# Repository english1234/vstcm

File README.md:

# VSTCM - the v.st Colour Mod - a colour vector graphics generator
The vstcm is a vector signal transceiver PCB which generates colour vector graphics to be displayed on an oscilloscope or vector monitor such as Amplifone, Wells Gardner WG6100, Hantarex MTRV and Electrohome G05, as used in Star Wars, Tempest, Gravitar, etc. 

When used with a computer (Raspberry Pi, PC, ...) running AdvanceMAME, it can be used to play classic colour (and monochrome) vector arcade games, but it can also play certain games all by itself using various emulators. If you search for vstcm on a well-known video sharing site you can see the board in action.

(Haven't got a vector monitor or an oscilloscope? Make your own, it's not that hard! - see below).

For those who built a V2 of this board, a document is provided to convert the wiring to run with V3 software.

The original v.st was designed by Trammell Hudson for black & white games. Documentation for that version can be found here https://github.com/osresearch/vst and here https://trmm.net/V.st/

Compared to the original version, the new vstcm adds:
- RGB colour with different intensity levels
- 6502, Z80 and 6809 emulators which allows it to play games on its own without a Raspberry Pi or MAME
- A mini version of MAME for playing vector games on the Teensy without a Raspberry Pi
- An upgrade to the Teensy 4.1 for more power (eg >800Mhz as opposed to 120Mhz for the Teensy 3.2)
- Asteroids style test patterns in Red, Green & Blue to aid CRT convergence
- A configuration menu with settings stored on the built in SD card
- Programmable onboard control buttons
- Programmable IR remote control buttons
- Extra pots to control X & Y position (to complement the existing X & Y size pots)
- Several power supply options: either USB, or external 5V/9V/12V

The board was built with simplicity in mind using components that are easy to find, and easy to solder so that anyone can build one.

## Programme code

Currently, the board can work in either of two ways:
- connected to a Raspberry Pi running MAME. The programme code for this option is a development of that which was provided with the original version of the v.st, with modifications made by "Swapfile" (Github user) to interface with AdvanceMAME, and then further modifications made by myself in order to add the new functionality specific to the vstcm, followed by extensive optimisation by fcawth (cf his fork of this project). There is scope for further improvement (see the wiki for this project in the link above), and it is hoped that the publication on github will encourage contributions to develop this as a relatively cheap and easy solution for the vector arcade / vector graphics community.
- on its own, running a 6502, Z80 or 6809 emulator, and with the original game ROM files stored on the SD card of the Teensy. So far, Battlezone, Asteroids and Donkey Kong work with this, but it shouldn't be too much trouble to get others working. Sound and external controls have not been properly implemented as yet (please feel free to contribute the necessary mods to the code...). See instructions below for how to get this to work.

## History of development

For those interested in seeing how things got to this point, the inital development of the PCB was documented with plenty of pictures (in French, but use Google Translate if required) here : https://www.gamoover.net/Forums/index.php?topic=43469.0 (from page 5) and also shows previous work on building vector arcade HV boards, an Amplifone deflection reproduction, an Asteroids game PCB reproduction, a bit of yoke rewinding, etc.

If you want to get in touch to ask questions, or contribute, I can be contacted at: robin@robinchampion.com or on Github (user english1234), Gamoover (english2), UKVAC (english2), KLOV (english2), as well as via the various vector graphics/Vectrex forums on Facebook.

A dedicated vstcm web page can be found here: https://robinchampion.com/vst_colour_mod.htm

Thread on KLOV: https://forums.arcade-museum.com/threads/announcing-the-vstcm-colour-vector-generator.505940/

Thread on UKVAC: http://www.ukvac.com/forum/announcing-the-vstcm-colour-vector-generator_topic388998_page1.html

## Getting the PCB built

A ZIP file is in the Gerbers directory. This can be uploaded to your PCB manufacturer of choice. It's a 2 sided 10cm x 10cm board so should be extremely cheap (JLPCB charged less than 5€ / $5 + shipping for 10 pieces in May 2022).

## Components

The BOM is in a dedicated folder and has Mouser references for many parts at the right hand side. 

- IC2: You need to choose if you are going to use an external supply or not and if so what voltage to use (5V, 9V or 12V). Recom makes these parts, but so do Traco and there may be other brands. Make sure there is a D (for double) at the end of the model number which generates +/- voltages, rather than the S (single) version. See power options below.
- The Molex parts are not strictly necessary, you may prefer something different or simply to solder wires directly to the holes in the PCB.
- U5: See power options below. I have also used a 7805 as a direct replacement with a small heatsink on it, which gets quite warm but hasn't burnt out as yet.
- optional IR remote: I really recommend this if you are putting the board inside a cabinet - see "IR remote programmable control buttons" below.
 
I would recommend socketing everything on the board (Teensy, DACs, Op Amps) so that they can be swapped out if better choices are found in the future.

Make sure you order short resistors, space for them on the board is tight.

## Power options for the PCB

The PCB can be powered in several ways (connect to J6):

|N° | Power supply option              | Supplies                                    | C3/C4    | IC2      | U5/C19/C20  | Split pad Teensy | Tested |
|---|----------------------------------|---------------------------------------------|----------|----------|-------------|------------------|--------|
| 1 | USB 5V                           | Complete circuit inc Teensy                 | Required | RB-0512D | Absent      | No               | No     |
| 2 | USB 5V + external 5V unregulated | USB supplies Teensy, external supplies rest | Required | RB-0512D | Absent      | No               | Yes    |
| 3 | External 9V unregulated          | Complete circuit inc Teensy                 | Required | RB-0912D | Present     | Yes              | No     |
| 4 | External 12V unregulated         | Complete circuit inc Teensy                 | Required | RB-1212D | Present     | Yes              | Yes    |
| 5 | USB 5V + external 12V regulated  | USB supplies Teensy, external supplies rest | Absent   | Absent   | Absent      | No               | Yes    |

1/ power the whole thing via USB from a Raspberry Pi: This requires a short good quality USB cable to work reliably. Make sure the Pi has at least a 3A supply. Since U5 is absent, bridge the two outer pins with a jumper wire.

2/ power the Teensy via USB from a Raspberry Pi, and use a separate external supply (such as a wall wart) for the DACs and Op Amps. 

3 & 4/ power the whole thing via an external supply which can be 9V or 12V (not 5V): this requires adding a LM2940T-5.0 regulator at U5 along with it's associated caps at C19 & C20, as well as cutting a link on the Teensy to ensure that it doesn't receive conflicting power from both the USB and the external supply. The RB-xx12D needs to be either a 9V or 12V model depending on the voltage of the external supply. A 5V supply won't work as the LM2940 requires over 6V to function according to its datasheet. 

The choice is really just a matter of what you have on hand. It makes no difference what vector CRT you have, as the output voltages of the PCB are the same whatever you use to power it. If you're connecting to an existing arcade machine, then chances are you have a +/-12V supply coming out of the power brick. Otherwise, many people have a box of old "wall wart" 5V (or 9V or 12V) adapters which will work fine: either fit a barrel connector to the PCB input or chop the connector off the end of the power supply and solder the 2 wires directly to the board (check with a multimeter first which is positive and which is ground). 

The easiest option is to use a 5V (option 2) as the LM2940 is not required, and you don't need to cut the link on the Teensy to separate USB and external power.
Do not use J7 unless you have thoroughly understood how the schematic works for the power supply.

## Schematic

This may seem obvious, but it's worth downloading Kicad in order to view the schematic and the PCB as there are some build notes on the schematic, and it will help you to understand the main sections of the PCB and how it all connects together. For the lazier, a PDF is available.

## Programming the Teensy

Follow the instructions on this page to download and install the Arduino environment and Teensyduino extension: https://www.pjrc.com/teensy/td_download.html
Use the Arduino software to load the .ino file in the Teensy code directory.

Connect the Teensy via USB to your computer.

Choose the Teensy 4.1 in the Teensyduino options, and overclock to 816Mhz, as well as the "Fastest" option. Make sure you have the latest version of Teensyduino.

Press the compile button. You may need to add the Bounce2 library if you don't already have it.

Press the upload button (or the button on the Teensy if it doesn't upload automatically).

(You can also use PlatformIO if you prefer).

There is a more detailed guide "How to programme the Teensy with the code for the VSTCM PCB.pdf" in the root directory.

## Testing the vstcm

Once the board is built and the Teensy programmed and fitted, it can be connected to your deflection board of choice (it has been tested on Amplifone, Wells Gardner WG6100, Electrohome G05 and Hantarex MTRV so far) and when powered on should show a test screen. It may be necessary to change the size and positions pots on the PCB as well as other controls on the deflection board (such as Z or colour gain).

Before connecting to the deflection board, it would probably be a good idea to make sure the vstcm is generating appropriate voltages at its outputs (preferably with an oscilloscope, or failing that with a decent multimeter). 

If you want to save changes to settings shown on the onscreen menu, then put a SD card in the Teensy (formatted with FAT32). After changing the settings to your requirements and pressing the middle button on the PCB, the vstcm.ini file will be created at the root of the SD card so that they can be reloaded at each boot. 

## Testing Battlezone with the 6502 emulator

Put the following ROM files on a SD card in a directory called roms/Battlezone: 036414a.01, 036413.01, 036412.01, 036411.01, 036410.01, 036409.01, 036422.01, 036421.01 (it's up to you to find them from somewhere...).

Put the SD card in the slot on the Teensy.

Upload the bzone.ino to the vstcm using the Arduino software.

Plug it in.

Switch on! 

If you have a IR remote then you can control the game in a rather basic manner for the moment... (press OK to start)

## Testing games with AdvanceMAME

A Raspberry Pi 4 or 400 is recommended (I have also tested with a Pi 3 Model B+ 2017 and an Orange Pi 3 LTS which seem to work ok too). If you are running the vstcm from the Raspberry/Orange Pi then a 3A supply would be preferable.
Other options are Windows, a Linux VM under Windows, native Linux or Mac (the latter of which I have not yet tested). 
I followed the instructions here to download and compile AdvanceMAME: https://www.arcade-projects.com/threads/almost-pixel-perfect-arcade-emulation-on-raspberry-pi-with-advancemame.7777/

Basically, there are just 7 commands on the Pi which are as follows:

```sudo apt-get install git autoconf automake libsdl2-dev libasound2-dev libfreetype6-dev zlib1g-dev libexpat1-dev libslang2-dev libncurses5-dev

git clone https://github.com/amadvance/advancemame.git

cd advancemame

sh autogen.sh

./configure

make -j3

sudo make install
```

You need to find some ROMs from somewhere and copy them into the ROM folder. I'm sure you'll manage to find them... The easiest way to get them on to the Pi is to set up a Samba share and copy them over from a PC.

Then to launch, type advmame followed by the name of the game.

If you're not getting output over the USB cable to the vstcm, then check the advmame.rc file and at the bottom make sure you have vector_aux_renderer set to dvg (instead of none) and vector_aux_renderer_port set to /dev/ttyACM0

The AdvanceMAME protocol for the USB DVG is here: https://github.com/amadvance/advancemame/blob/master/advance/osd/dvg.c 

You can change the settings on the VSTCM during a game by pressing the left and right buttons on the PCB simultaneously to display the menu as an overlay.

## IR remote programmable control buttons

For £1 / $1 / 1€ you can get a HX1838 infra red adapter board with remote control, wiring, everything you need in fact. There are only 3 wires to connect: 5V, GND and signal. I soldered pin headers in the holes provided on either side of the Teensy, and put 5V on the bottom left hand hole of the Teensy (to left of USB socket), GND on the bottom right pin of the Teensy, and signal on pin 32 (top right hand pin of Teensy). 

This might seem like a bit of a gadget, but when you are spending your time going behind the arcade cab to press a button, coming back round the front to see the effect on the screen, and doing this over and over again, the advantages become obvious! 

The IR sensor is the size of an LED and so very easy to hide somewhere at the front of an arcade cab, and then you can just change the settings at will while you look at the screen.

## Haven't got a vector monitor or an oscilloscope?

Apart from this PCB, you need a CRT, a high voltage board, a deflection board and a power supply to make a complete vector monitor. There are solutions for all of these parts:

CRT - I'm using a 19"/48cm Philips TV bought for pennies through the small ads. You need to rewind the yoke using magnet wire. There is an excellent video by Jason Kopp here which explains all: https://youtu.be/Ci9qiGVMF7s I experimented on a 5" b&w security monitor first, then went for the big screen. Avoid Trinitrons and PC monitors, you need a basic no frills TV tube. It took me several attempts to get it more or less right, but I still have some wires which are not completely straight and the result seems to be the slightly bent vectors visible in the top right hand corner of my screen in the photo of the test screen above. The whole thing really wasn't hard, it just requires patience.

High voltage: Amplifone and Wells Gardner 6100 blank PCBs are available online, and there are also fully built solutions (see the various vector groups on Facebook) available new or second hand from the usual auction sites and specialist arcade sellers (mostly USA based).

Deflection board: I bought a second hand non working Amplifone and then fixed it (which wasn't hard, plenty of info online), but new PCBs are available online, and a Wells Gardner WG6100 should work too.

Power supply: the CRT and deflection board can be run either from an old Atari power brick, or else by wiring together two cheap 24V power supplies from Aliexpress in order to provide +/- 24V which satisfies the requirement for 50VAC on a Amplifone colour vector monitor. The CRT needs 6.3V for the heater filament, which I'm getting from an Atari power brick using the supply meant for the coin door, but there are other solutions if you look online (hint: 6.3V is frequently required for valve amp projects). If you find the right Atari power brick, it will power the whole thing: CRT, HV, deflection, Raspberry Pi and vstcm.

There's plenty of discussion of solutions to these problems on KLOV, UKVAC, and the FB vector forums with plenty of knowledgeable people able to answer questions. Also there are a fair few videos on Youtube going from theory to practice. Again, it's not that hard, so give it a go!

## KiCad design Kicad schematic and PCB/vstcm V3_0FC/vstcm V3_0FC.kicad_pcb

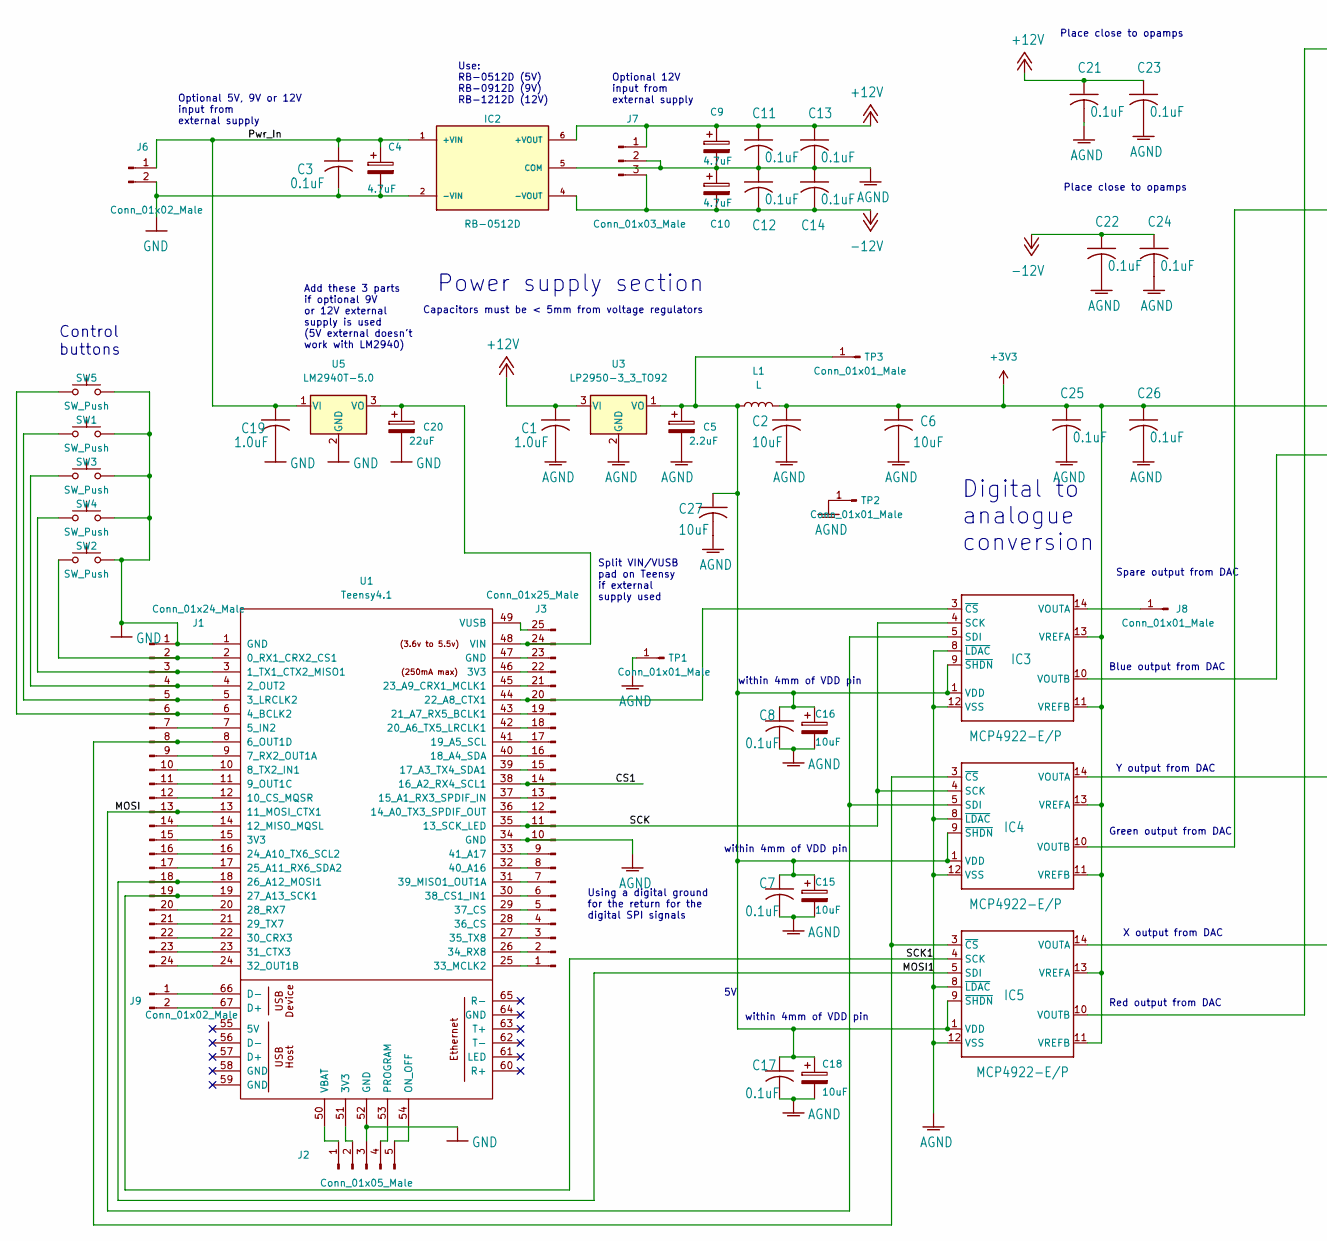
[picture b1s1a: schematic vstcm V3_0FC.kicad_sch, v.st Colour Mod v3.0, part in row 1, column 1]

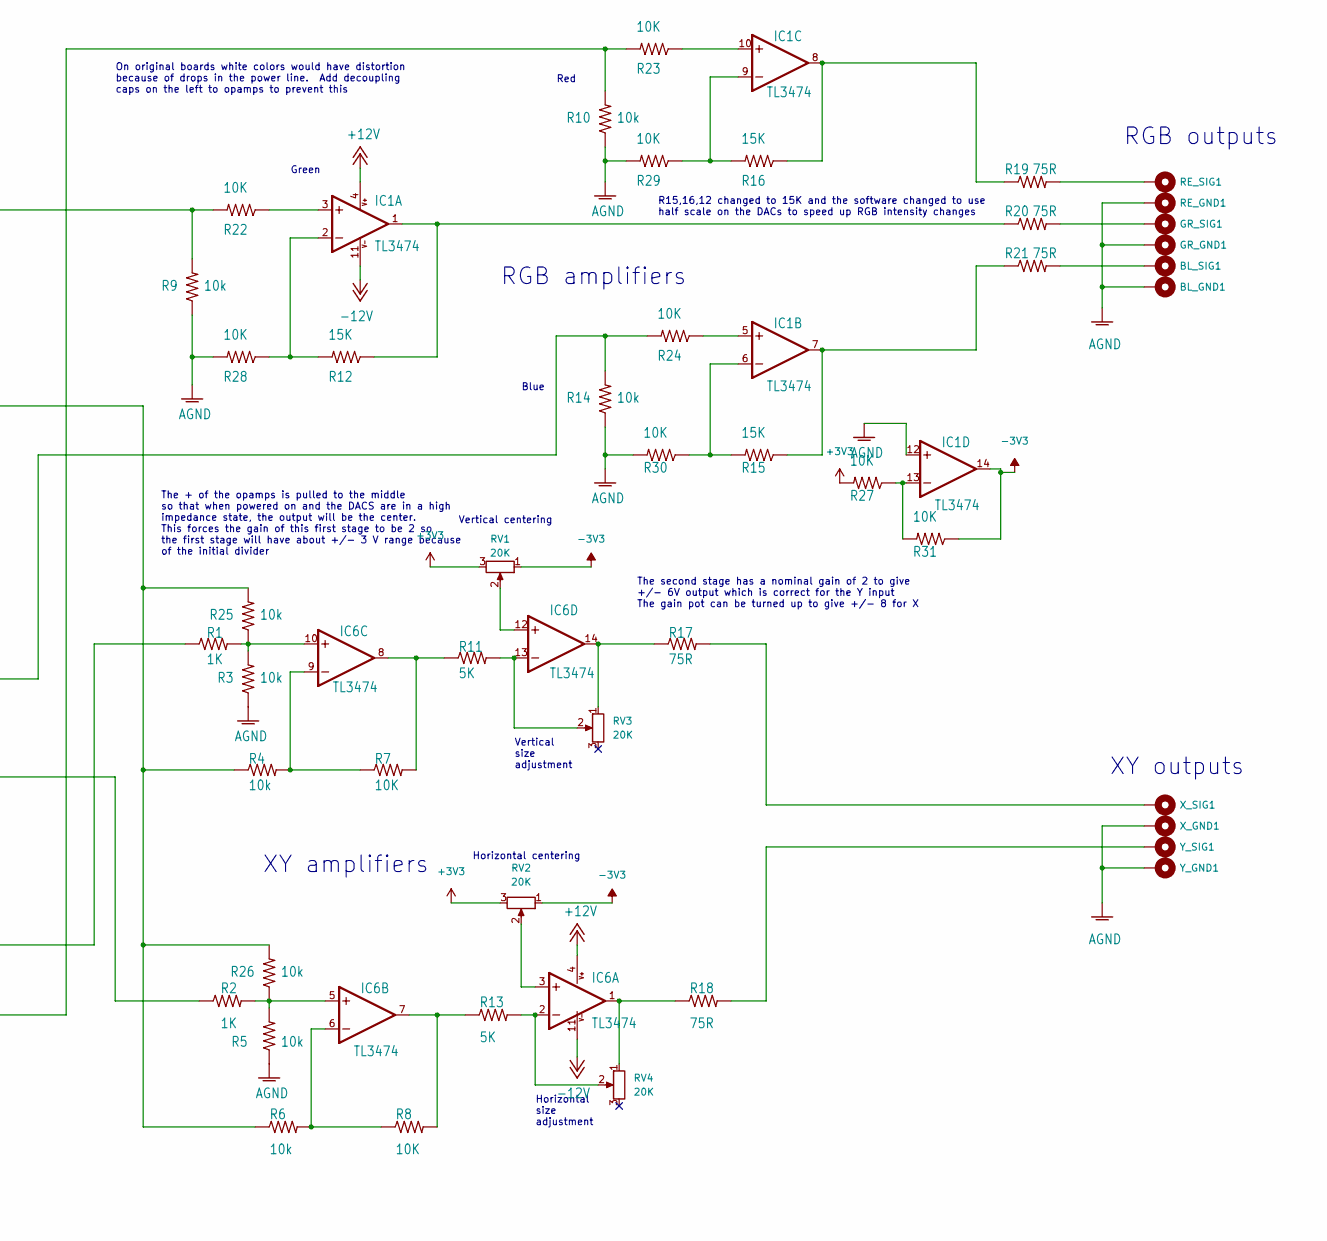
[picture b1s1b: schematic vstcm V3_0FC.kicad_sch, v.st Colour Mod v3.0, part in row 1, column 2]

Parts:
BL_GND1: MountingHole_Pad; MountingHole_2.2mm_M2_DIN965_Pad_TopBottom
BL_SIG1: MountingHole_Pad; MountingHole_2.2mm_M2_DIN965_Pad_TopBottom
C1, C19: 1.0uF; C_Disc_D5.0mm_W2.5mm_P2.50mm
C2, C6, C27: 10uF; C_Disc_D5.0mm_W2.5mm_P2.50mm
C3, C7, C8, C11, C12, C13, C14, C17, C21, C22, C23, C24, C25, C26: 0.1uF; C_Disc_D5.0mm_W2.5mm_P2.50mm
C4, C9, C10: 4.7uF; CP_Radial_D5.0mm_P2.00mm
C5: 2.2uF; CP_Radial_D5.0mm_P2.00mm
C15, C16, C18: 10uF; CP_Radial_D5.0mm_P2.00mm
C20: 22uF; CP_Radial_D5.0mm_P2.00mm
GR_GND1: MountingHole_Pad; MountingHole_2.2mm_M2_DIN965_Pad_TopBottom
GR_SIG1: MountingHole_Pad; MountingHole_2.2mm_M2_DIN965_Pad_TopBottom
IC1, IC6: TL3474; DIP-14_W7.62mm_Socket
IC2: RB-0512D; RECOM_0512D; PARTREV 0/2015
IC3, IC4, IC5: MCP4922-E/P; DIP-14_W7.62mm_Socket
J1: Conn_01x24_Male; PinHeader_1x24_P2.54mm_Vertical
J2: Conn_01x05_Male; PinHeader_1x05_P2.54mm_Vertical
J3: Conn_01x25_Male; PinHeader_1x25_P2.54mm_Vertical
J6: Conn_01x02_Male; Molex_KK-254_AE-6410-02A_1x02_P2.54mm_Vertical
J7: Conn_01x03_Male; Molex_KK-254_AE-6410-03A_1x03_P2.54mm_Vertical
J8: Conn_01x01_Male; PinHeader_1x01_P2.54mm_Vertical
J9: Conn_01x02_Male; PinHeader_1x02_P2.54mm_Vertical
L1: L; L_Axial_L12.0mm_D5.0mm_P15.24mm_Horizontal_Fastron_MISC
R1, R2: 1K; R_Axial_DIN0207_L6.3mm_D2.5mm_P7.62mm_Horizontal
R3, R4, R5, R6, R9, R10, R14, R25, R26: 10k; R_Axial_DIN0207_L6.3mm_D2.5mm_P7.62mm_Horizontal
R7, R8, R22, R23, R24, R27, R28, R29, R30, R31: 10K; R_Axial_DIN0207_L6.3mm_D2.5mm_P7.62mm_Horizontal
R11, R13: 5K; R_Axial_DIN0207_L6.3mm_D2.5mm_P7.62mm_Horizontal
R12, R15, R16: 15K; R_Axial_DIN0207_L6.3mm_D2.5mm_P7.62mm_Horizontal
R17, R18, R19, R20, R21: 75R; R_Axial_DIN0207_L6.3mm_D2.5mm_P7.62mm_Horizontal
RE_GND1: MountingHole_Pad; MountingHole_2.2mm_M2_DIN965_Pad_TopBottom
RE_SIG1: MountingHole_Pad; MountingHole_2.2mm_M2_DIN965_Pad_TopBottom
RV1, RV2, RV3, RV4: 20K; Potentiometer_Bourns_3386P_Vertical
SW1, SW2, SW3, SW4, SW5: SW_Push; SW_PUSH_6mm_H4.3mm
TP1, TP2, TP3: Conn_01x01_Male; PinHeader_1x01_P2.54mm_Vertical
U1: Teensy4.1; Teensy41
U3: LP2950-3_3_TO92; TO-92
U5: LM2940T-5.0; TO-220-3_Vertical
X_GND1: MountingHole_Pad; MountingHole_2.2mm_M2_DIN965_Pad_TopBottom
X_SIG1: MountingHole_Pad; MountingHole_2.2mm_M2_DIN965_Pad_TopBottom
Y_GND1: MountingHole_Pad; MountingHole_2.2mm_M2_DIN965_Pad_TopBottom
Y_SIG1: MountingHole_Pad; MountingHole_2.2mm_M2_DIN965_Pad_TopBottom

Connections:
+3V3: C2.1, C6.1, C25.1, C26.1, IC3.11 (VREFB), IC3.13 (VREFA), IC4.11 (VREFB), IC4.13 (VREFA), IC5.11 (VREFB), IC5.13 (VREFA), L1.2, R4.1, R6.1, R25.2, R26.2, R27.2, RV1.3, RV2.3
+12V: C1.1, C9.1, C11.1, C13.1, C21.1, C23.1, IC1.4 (V+), IC2.6 (+VOUT), IC6.4 (V+), J7.1, U3.3 (VI)
-3V3: IC1.14 (OUT), R31.1, RV1.1, RV2.1
-12V: C10.2, C12.2, C14.2, C22.1, C24.1, IC1.11 (V-), IC2.4 (-VOUT), IC6.11 (V-), J7.3
/CS1: J3.14, U1.38 (16_A2_RX4_SCL1)
/MOSI: IC3.5 (SDI), IC4.5 (SDI), J1.13, U1.13 (11_MOSI_CTX1)
/MOSI1: IC5.5 (SDI), J1.18, U1.18 (26_A12_MOSI1)
/Pwr_In: C3.1, C4.1, C19.1, IC2.1 (+VIN), J6.1, U5.1 (VI)
/SCK: IC3.4 (SCK), IC4.4 (SCK), J3.11, U1.35 (13_SCK_LED)
/SCK1: IC5.4 (SCK), J1.19, U1.19 (27_A13_SCK1)
AGND: BL_GND1.1, C1.2, C2.2, C5.2, C6.2, C7.2, C8.2, C9.2, C10.1, C11.2, C12.1, C13.2, C14.1, C15.2, C16.2, C17.2, C18.2, C21.2, C22.2, C23.2, C24.2, C25.2, C26.2, C27.2, GR_GND1.1, IC1.12 (+IN), IC2.5 (COM), IC3.8 (~LDAC), IC3.12 (VSS), IC4.8 (~LDAC), IC4.12 (VSS), IC5.8 (~LDAC), IC5.12 (VSS), J3.10, J7.2, R3.1, R5.1, R9.1, R10.1, R14.1, R28.2, R29.2, R30.2, RE_GND1.1, TP1.1, TP2.1, U1.34 (GND), U3.2 (GND), X_GND1.1, Y_GND1.1
GND: C3.2, C4.2, C19.2, C20.2, IC2.2 (-VIN), J1.1, J2.3, J6.2, SW1.2, SW2.1, SW3.2, SW4.2, SW5.1, U1.1 (GND), U1.52 (GND), U5.2 (GND)
unnamed: BL_SIG1.1, R21.2
unnamed: C5.1, C7.1, C8.1, C15.1, C16.1, C17.1, C18.1, C27.1, IC3.1 (VDD), IC3.9 (~SHDN), IC4.1 (VDD), IC4.9 (~SHDN), IC5.1 (VDD), IC5.9 (~SHDN), L1.1, TP3.1, U3.1 (VO)
unnamed: C20.1, J3.24, U1.48 (VIN), U5.3 (VO)
unnamed: GR_SIG1.1, R20.2
unnamed: IC1.1 (OUT), R12.1, R20.1
unnamed: IC1.2 (-IN), R12.2, R28.1
unnamed: IC1.3 (+IN), R22.1
unnamed: IC1.5 (+IN), R24.1
unnamed: IC1.6 (-IN), R15.2, R30.1
unnamed: IC1.7 (OUT), R15.1, R21.1
unnamed: IC1.8 (OUT), R16.1, R19.1
unnamed: IC1.9 (-IN), R16.2, R29.1
unnamed: IC1.10 (+IN), R23.1
unnamed: IC1.13 (-IN), R27.1, R31.2
unnamed: IC3.3 (~CS), J3.20, U1.44 (22_A8_CTX1)
unnamed: IC3.10 (VOUTB), R14.2, R24.2
unnamed: IC3.14 (VOUTA), J8.1
unnamed: IC4.3 (~CS), IC5.3 (~CS), J1.8, U1.8 (6_OUT1D)
unnamed: IC4.10 (VOUTB), R9.2, R22.2
unnamed: IC4.14 (VOUTA), R2.1
unnamed: IC5.10 (VOUTB), R10.2, R23.2
unnamed: IC5.14 (VOUTA), R1.1
unnamed: IC6.1 (OUT), R18.1, RV4.1
unnamed: IC6.2 (-IN), R13.2, RV4.2
unnamed: IC6.3 (+IN), RV2.2
unnamed: IC6.5 (+IN), R2.2, R5.2, R26.1
unnamed: IC6.6 (-IN), R6.2, R8.1
unnamed: IC6.7 (OUT), R8.2, R13.1
unnamed: IC6.8 (OUT), R7.2, R11.1
unnamed: IC6.9 (-IN), R4.2, R7.1
unnamed: IC6.10 (+IN), R1.2, R3.2, R25.1
unnamed: IC6.12 (+IN), RV1.2
unnamed: IC6.13 (-IN), R11.2, RV3.2
unnamed: IC6.14 (OUT), R17.1, RV3.1
unnamed: J1.2, SW2.2, U1.2 (0_RX1_CRX2_CS1)
unnamed: J1.3, SW4.1, U1.3 (1_TX1_CTX2_MISO1)
unnamed: J1.4, SW3.1, U1.4 (2_OUT2)
unnamed: J1.5, SW1.1, U1.5 (3_LRCLK2)
unnamed: J1.6, SW5.2, U1.6 (4_BCLK2)
unnamed: J1.7, U1.7 (5_IN2)
unnamed: J1.9, U1.9 (7_RX2_OUT1A)
unnamed: J1.10, U1.10 (8_TX2_IN1)
unnamed: J1.11, U1.11 (9_OUT1C)
unnamed: J1.12, U1.12 (10_CS_MQSR)
unnamed: J1.14, U1.14 (12_MISO_MQSL)
unnamed: J1.15, U1.15 (3V3)
unnamed: J1.16, U1.16 (24_A10_TX6_SCL2)
unnamed: J1.17, U1.17 (25_A11_RX6_SDA2)
unnamed: J1.20, U1.20 (28_RX7)
unnamed: J1.21, U1.21 (29_TX7)
unnamed: J1.22, U1.22 (30_CRX3)
unnamed: J1.23, U1.23 (31_CTX3)
unnamed: J1.24, U1.24 (32_OUT1B)
unnamed: J2.1, U1.50 (VBAT)
unnamed: J2.2, U1.51 (3V3)
unnamed: J2.4, U1.53 (PROGRAM)
unnamed: J2.5, U1.54 (ON_OFF)
unnamed: J3.1, U1.25 (33_MCLK2)
unnamed: J3.2, U1.26 (34_RX8)
unnamed: J3.3, U1.27 (35_TX8)
unnamed: J3.4, U1.28 (36_CS)
unnamed: J3.5, U1.29 (37_CS)
unnamed: J3.6, U1.30 (38_CS1_IN1)
unnamed: J3.7, U1.31 (39_MISO1_OUT1A)
unnamed: J3.8, U1.32 (40_A16)
unnamed: J3.9, U1.33 (41_A17)
unnamed: J3.12, U1.36 (14_A0_TX3_SPDIF_OUT)
unnamed: J3.13, U1.37 (15_A1_RX3_SPDIF_IN)
unnamed: J3.15, U1.39 (17_A3_TX4_SDA1)
unnamed: J3.16, U1.40 (18_A4_SDA)
unnamed: J3.17, U1.41 (19_A5_SCL)
unnamed: J3.18, U1.42 (20_A6_TX5_LRCLK1)
unnamed: J3.19, U1.43 (21_A7_RX5_BCLK1)
unnamed: J3.21, U1.45 (23_A9_CRX1_MCLK1)
unnamed: J3.22, U1.46 (3V3)
unnamed: J3.23, U1.47 (GND)
unnamed: J3.25, U1.49 (VUSB)
unnamed: J9.1, U1.66 (D-)
unnamed: J9.2, U1.67 (D+)
unnamed: R17.2, X_SIG1.1
unnamed: R18.2, Y_SIG1.1
unnamed: R19.2, RE_SIG1.1

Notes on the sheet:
Red output from DAC
Using a digital ground for the return for the digital SPI signals
Horizontal size adjustment
Vertical size adjustment
XY outputs
within 4mm of VDD pin
X output from DAC
Red
Green
Vertical centering
Blue output from DAC
Control buttons
The + of the opamps is pulled to the middle so that when powered on and the DACS are in a high impedance state, the output will be the center. This forces the gain of this first stage to be 2 so the first stage will have about +/- 3 V range because of the initial divider
Power supply section
The second stage has a nominal gain of 2 to give +/- 6V output which is correct for the Y input The gain pot can be turned up to give +/- 8 for X
Blue
Spare output from DAC
R15,16,12 changed to 15K and the software changed to use half scale on the DACs to speed up RGB intensity changes
Digital to analogue conversion
Place close to opamps
Split VIN/VUSB pad on Teensy if external supply used
Optional 5V, 9V or 12V input from external supply
Use: RB-0512D (5V) RB-0912D (9V) RB-1212D (12V)
Horizontal centering
Green output from DAC
XY amplifiers
On original boards white colors would have distortion because of drops in the power line. Add decoupling caps on the left to opamps to prevent this
Add these 3 parts if optional 9V or 12V external supply is used (5V external doesn't work with LM2940)
Optional 12V input from external supply
Capacitors must be < 5mm from voltage regulators
Y output from DAC
RGB outputs
RGB amplifiers

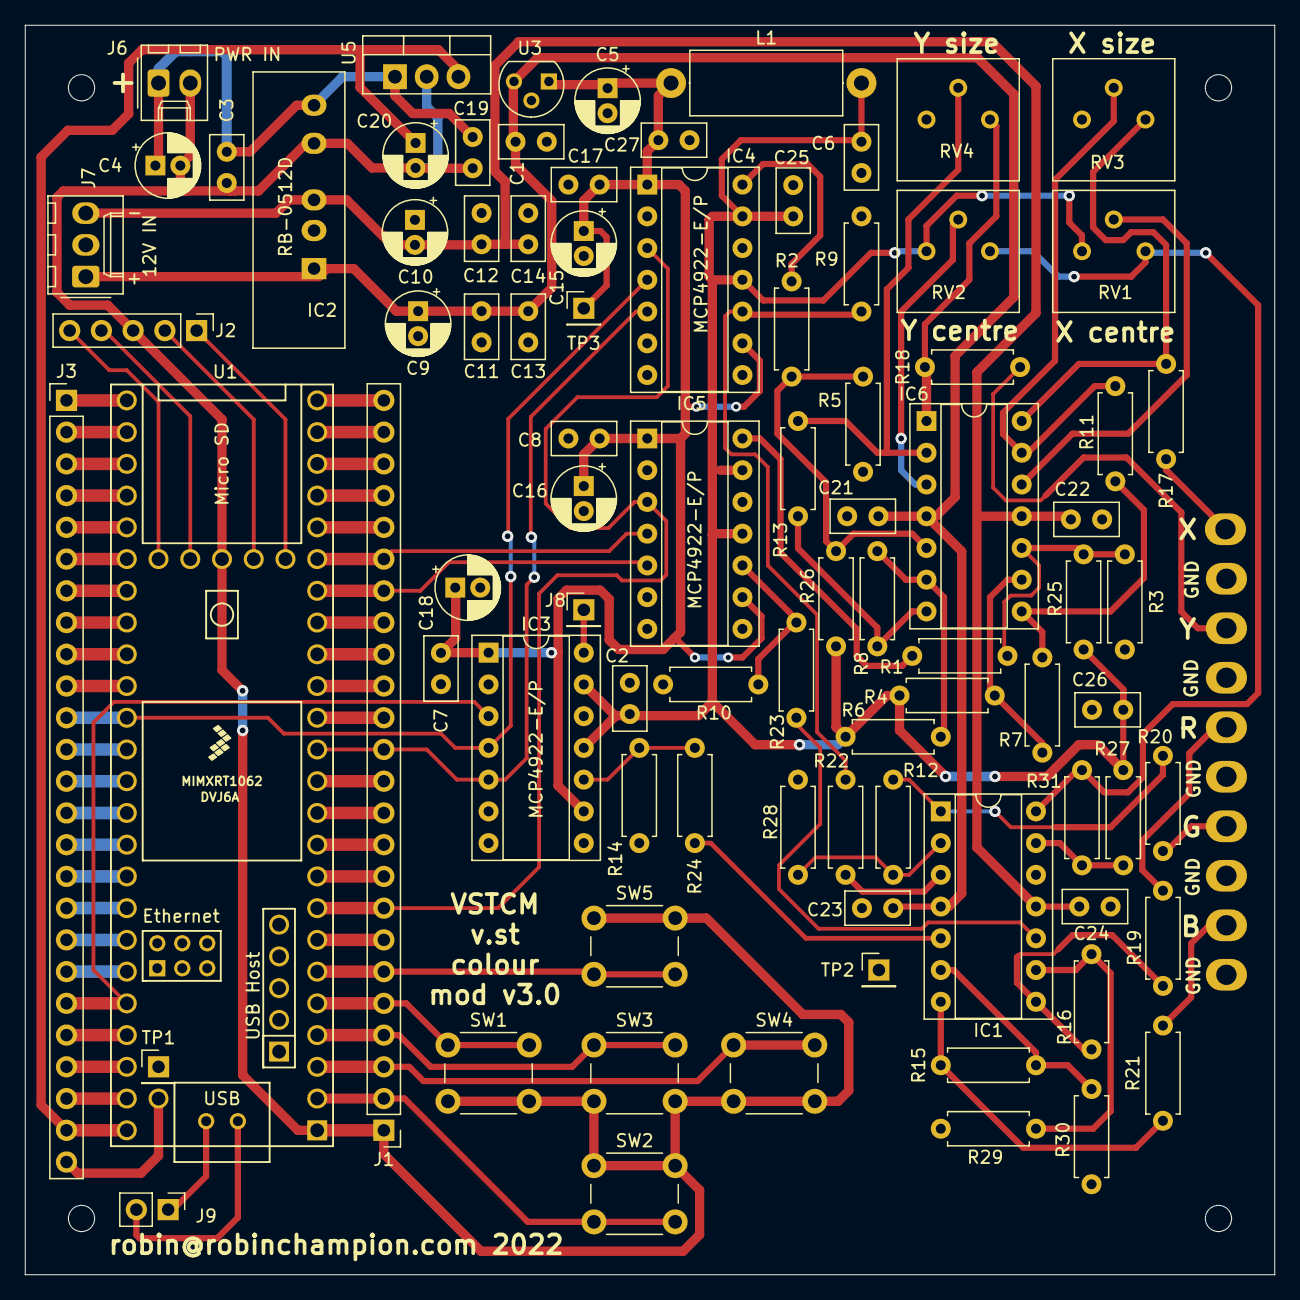
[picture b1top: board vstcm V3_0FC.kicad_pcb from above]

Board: 2 copper layers, 100.0 x 100.0 mm, 101 parts (0 on the bottom side), 94 nets.

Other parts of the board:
REF01, REF02, REF03, REF04: MountingHole_2.1mm

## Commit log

2022-05-19 Delete teensyv-sch.pdf
    Deleted v2 to replace with v2.1 which has a corrected symbol and connections for U5.
2022-05-19 Add files via upload
    v2.1 has a corrected symbol and connections for U5.
2022-05-19 Add files via upload
    v2.1 with corrected pin order for U5.
2022-05-28 Update BOM teensyv.txt
    U4 is no longer needed and should be jumpered
2022-05-30 Update vst_Colour_Mod_v2_Teensy_41.ino
    Addition of IR remote functionality to control settings from the front of an arcade cab
2022-06-03 Update README.md
    Added info on building the other parts of a vector monitor
2022-06-03 Update vst_Colour_Mod_v2_Teensy_41.ino
    Improvements to settings selection
2022-06-03 Update vst_Colour_Mod_v2_Teensy_41.ino
    Added Red, Green and Blue Asteroids style test patterns to aid in CRT convergence.
2022-06-06 repair build when IR_REMOTE is disabled. fix a few warnings.
2022-06-06 Update README.md
    Simplified power options using a table
2022-06-06 Update vst_Colour_Mod_v2_Teensy_41.ino
    Removed a few unneeded lines of code
2022-06-12 Update README.md
    Addition of 6502 emulator to play games autonomously
2022-06-12 Add files via upload
    Code to run a 6502 emulator (rough port of vecsim) playing Battlezone (not including ROM files)
2022-06-29 Update vst_Colour_Mod_v2_Teensy_41.ino
    Added debounce routines for the control buttons, plus minor optimisations
2022-06-29 Update README.md
    Added a comment about debouncing
2022-06-29 Add files via upload
    Settings file stored on SD card
2022-06-29 Update vst_Colour_Mod_v2_Teensy_41.ino
    Settings are now stored on SD card. Code to write to settings file not yet written.
2022-06-30 Update vst_Colour_Mod_v2_Teensy_41.ino
    Writing settings to the SD card now works. Use the centre button or OK on the IR remote to save settings.
2022-06-30 Update README.md
    Battlezone can now be controlled using the IR remote
2022-06-30 Update bzone.ino
    The game can now be controlled using the IR remote
2022-07-15 Update vst_Colour_Mod_v2_Teensy_41.ino
    Incorporating speed mods developed by fcawth (no hardware changes required to PCB v2 at this point)
2022-07-15 Rename BOM teensyv.txt to BOM/BOM vstcm v2.txt
    File moved and renamed explicitly to v2 in anticipation of v3
2022-07-15 Moved to v2 directory
2022-07-15 Created placeholders for forthcoming v3
2022-07-18 Update README.md
    The recommended value for R12, R15 & R16 is now 3.6K instead of 68R.
2022-07-18 R12, R15, R16 now 3.6K
2022-07-18 Update vst_Colour_Mod_v2_Teensy_41.ino
    Incorporating mods made by fcawth: improvements to AdvanceMAME handshake, tweaks to default settings values, beam settling delay handled better, button management shifted to end of main loop to preve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
2022-07-18 Put into bzone folder
2022-07-18 Renamed folder
2022-07-20 Update bzone.ino
    Experimental sound playing RAW format .hex files
2022-07-20 Update bzone.h
    Experimental sound using RAW format
2022-07-22 First commit with no controls, sound or z blanking
2022-07-22 Put in v2 folder
2022-07-23 Update tailgunner.ino
    Improvements to screen size and geometry, corrected screen foldover.
2022-08-26 Vector font demo
2022-08-29 Reorganise folders and archive V2
2022-08-29 Update with V3 schematic and code
2022-08-30 Hershey font used in place of Asteroids. Source split up into functional blocks.
2022-08-30 Generation of Gerber files
2022-08-30 Updated to V3
2022-08-30 More updates relevant to V3
2022-09-03 Spot killer adjustment and tuning
    The spot killer moves will now happen if there is enough time in the frame, even if the min and max are in range. This keeps the spot killer on the newer 6100s and repros (most sensitive) from trigge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
2022-09-03 More spot killer tuning
    The eliminator high score screen was triggering the spot killer. Adjusted the limits to make it do the double moves for dwell time>10
    Also changed json version to 3.0 instead of 3.0FC - json support should be fixed at some point.
2022-09-03 Even more settings tweaks
2022-09-03 Increase spot killer delay if there is enough time
2022-09-04 Fixed IR Remote code
    IR remote define was in the vst_color_Mod_V3.cpp file so it was not being seen by buttons.cpp so the remote did not work. Moved the remote -related code to the relevant files
2022-09-09 vfont folder created to enable compilation
2022-09-09 Added splash screen and integrated Battlezone emulator
2022-10-06 Update README.md
    Added 6th power option: external 5V regulated supply
2022-10-06 Update README.md
    Battlezone now works on both V2 and V3
2022-10-17 Add files via upload
    Added document describing changes required to convert PCB V2 DAC outputs to V3
2022-12-04 Incorporated Cinematronics emulator and other improvements
2022-12-04 Added Vector Donkey Kong running on MAME on the Teensy
2023-03-28 Added debug for Windows
    New version of code which can be compiled for Teensy or Windows to facilitate debugging
2023-04-04 Added monochrome display option
    Added new setting to choose between monochrome and colour displays. The max value of RGB is used as the Z value for monochrome.
2023-04-04 Reinstated SWAP_XY setting
2023-10-01 Update README.md
    Tested successfully on Hantarex MTRV
2024-01-21 Updated U3 from 5V to 3.3V
    Corrected U3 LP2950 requires a 3.3V output instead of 5V
2024-01-21 Animated vector fonts is a demo
2024-01-21 Various updates
2024-02-01 Added a guide to programming the Teensy with code for VSTCM
    Added a guide to programming the Teensy with code for VSTCM
2024-09-04 Update BOM vstcm v3.txt
    Add part numbers for some resistors that were missing.
2024-09-06 Deleted unneeded backup files
    Deleted unneeded backup files
2024-09-06 Added Teensy and deleted inductor L1
2024-09-06 Added IC sockets
2024-09-07 More info on type of IC sockets and mounting for Teensy; Kicad files updated to v8.
2025-01-20 Various extra comments added to the code
2025-04-09 Added that U5 needs to be bridged if powering everything from USB
    Added that U5 needs to be bridged if powering everything from USB
2025-04-09 SD card formatted to FAT32
    SD card formatted to FAT32
2025-04-09 Info on SD Card
    Info on SD Card
2025-04-10 Multiple updates to code
    Multiple updates to code
2025-04-11 Corrected bug to make settings buttons work when playing a game over USB
2025-04-11 Added instructions for accessing settings menu during a game
2025-04-12 Gravitar & Space Duel sort of working and in colour
2025-06-05 Fix for compiler error
    Fix for compiler error
2025-06-14 Multiple changes to refactor the menu system and get Gravitar, Space Duel and Black Widow working
2025-06-15 Various bug fixes
2025-06-15 Space Duel colour correction
2025-07-14 Power supply
2026-06-04 Old more stable version
    Older version of code which is more stable when using AdvanceMAME on PC
